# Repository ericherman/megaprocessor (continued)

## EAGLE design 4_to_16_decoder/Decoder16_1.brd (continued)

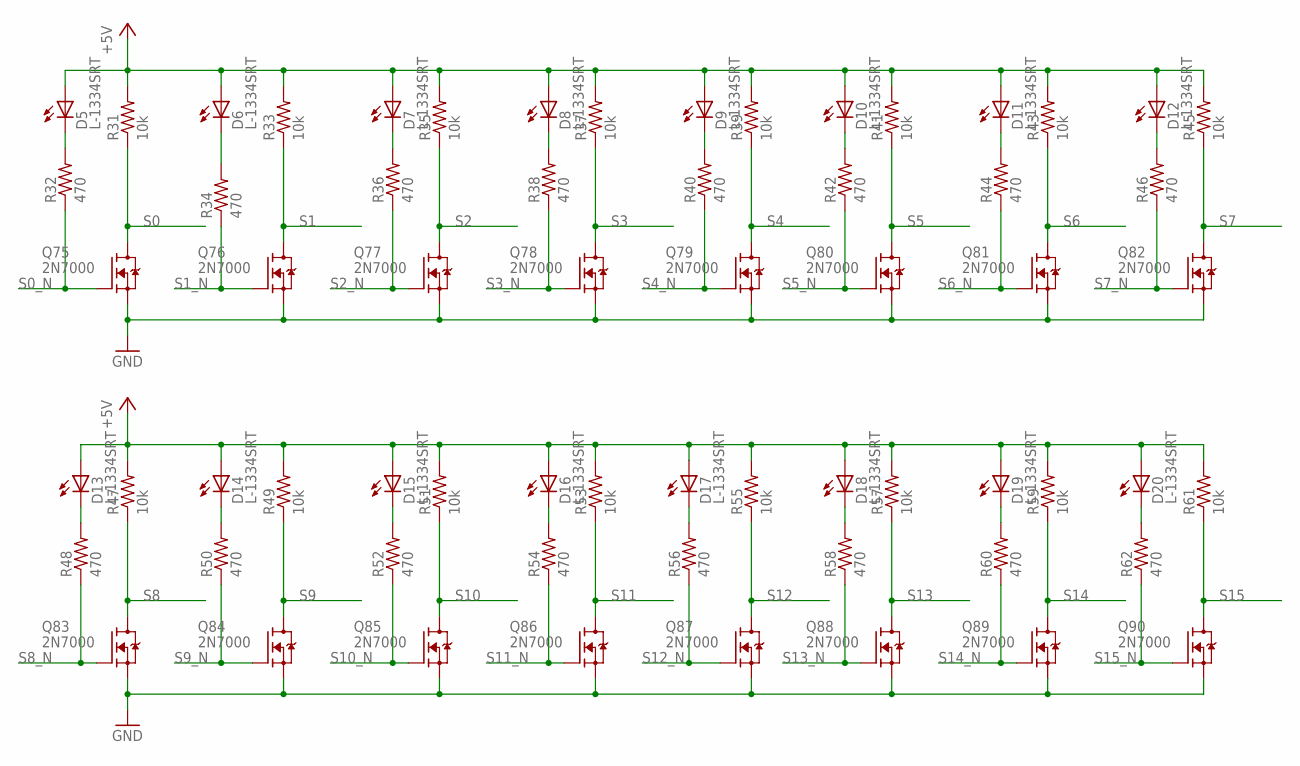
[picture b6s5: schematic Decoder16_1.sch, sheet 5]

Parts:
D5, D6, D7, D8, D9, D10, D11, D12, D13, D14, D15, D16, D17, D18, D19, D20: L-1334SRT; LED3MM
Q75, Q76, Q77, Q78, Q79, Q80, Q81, Q82, Q83, Q84, Q85, Q86, Q87, Q88, Q89, Q90: 2N7000; TO92-DGS
R31, R33, R35, R37, R39, R41, R43, R45, R47, R49, R51, R53, R55, R57, R59, R61: 10k; R_P2INCH
R32, R34, R36, R38, R40, R42, R44, R46, R48, R50, R52, R54, R56, R58, R60, R62: 470; R_P2INCH

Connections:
+5V: D5.A, D6.A, D7.A, D8.A, D9.A, D10.A, D11.A, D12.A, D13.A, D14.A, D15.A, D16.A, D17.A, D18.A, D19.A, D20.A, R31.2, R33.2, R35.2, R37.2, R39.2, R41.2, R43.2, R45.2, R47.2, R49.2, R51.2, R53.2, R55.2, R57.2, R59.2, R61.2; also elsewhere on the board
GND: Q75.S, Q76.S, Q77.S, Q78.S, Q79.S, Q80.S, Q81.S, Q82.S, Q83.S, Q84.S, Q85.S, Q86.S, Q87.S, Q88.S, Q89.S, Q90.S; also elsewhere on the board
unnamed: D5.K (C), R32.2
unnamed: D13.K (C), R48.2
unnamed: D6.K (C), R34.2
unnamed: D14.K (C), R50.2
unnamed: D7.K (C), R36.2
unnamed: D15.K (C), R52.2
unnamed: D8.K (C), R38.2
unnamed: D16.K (C), R54.2
unnamed: D9.K (C), R40.2
unnamed: D17.K (C), R56.2
unnamed: D10.K (C), R42.2
unnamed: D18.K (C), R58.2
unnamed: D11.K (C), R44.2
unnamed: D19.K (C), R60.2
unnamed: D12.K (C), R46.2
unnamed: D20.K (C), R62.2
S0: Q75.D, R31.1; also elsewhere on the board
S0_N: Q75.G, R32.1; also elsewhere on the board
S1: Q76.D, R33.1; also elsewhere on the board
S1_N: Q76.G, R34.1; also elsewhere on the board
S2: Q77.D, R35.1; also elsewhere on the board
S2_N: Q77.G, R36.1; also elsewhere on the board
S3: Q78.D, R37.1; also elsewhere on the board
S3_N: Q78.G, R38.1; also elsewhere on the board
S4: Q79.D, R39.1; also elsewhere on the board
S4_N: Q79.G, R40.1; also elsewhere on the board
S5: Q80.D, R41.1; also elsewhere on the board
S5_N: Q80.G, R42.1; also elsewhere on the board
S6: Q81.D, R43.1; also elsewhere on the board
S6_N: Q81.G, R44.1; also elsewhere on the board
S7: Q82.D, R45.1; also elsewhere on the board
S7_N: Q82.G, R46.1; also elsewhere on the board
S8: Q83.D, R47.1; also elsewhere on the board
S8_N: Q83.G, R48.1; also elsewhere on the board
S9: Q84.D, R49.1; also elsewhere on the board
S9_N: Q84.G, R50.1; also elsewhere on the board
S10: Q85.D, R51.1; also elsewhere on the board
S10_N: Q85.G, R52.1; also elsewhere on the board
S11: Q86.D, R53.1; also elsewhere on the board
S11_N: Q86.G, R54.1; also elsewhere on the board
S12: Q87.D, R55.1; also elsewhere on the board
S12_N: Q87.G, R56.1; also elsewhere on the board
S13: Q88.D, R57.1; also elsewhere on the board
S13_N: Q88.G, R58.1; also elsewhere on the board
S14: Q89.D, R59.1; also elsewhere on the board
S14_N: Q89.G, R60.1; also elsewhere on the board
S15: Q90.D, R61.1; also elsewhere on the board
S15_N: Q90.G, R62.1; also elsewhere on the board

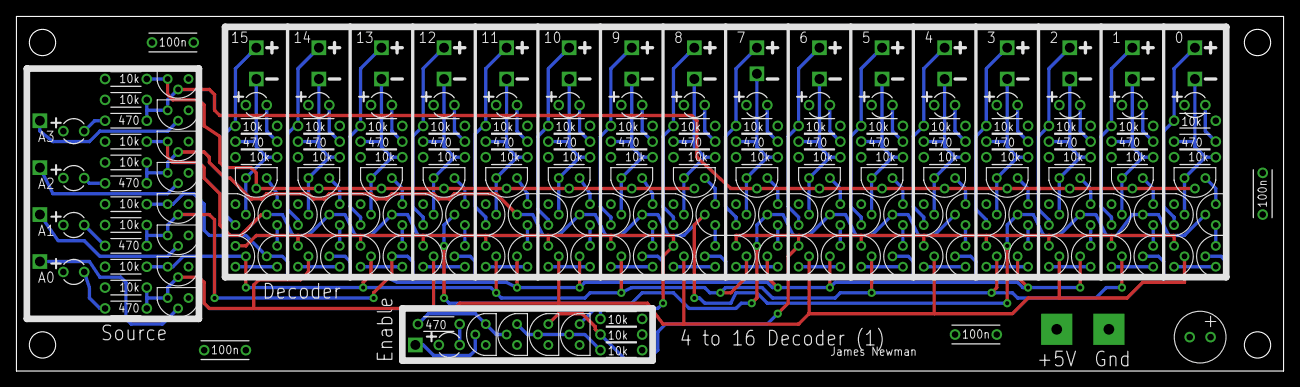
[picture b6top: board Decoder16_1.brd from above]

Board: 4 copper layers, 154.3 x 43.2 mm, 225 parts (0 on the bottom side), 120 nets.

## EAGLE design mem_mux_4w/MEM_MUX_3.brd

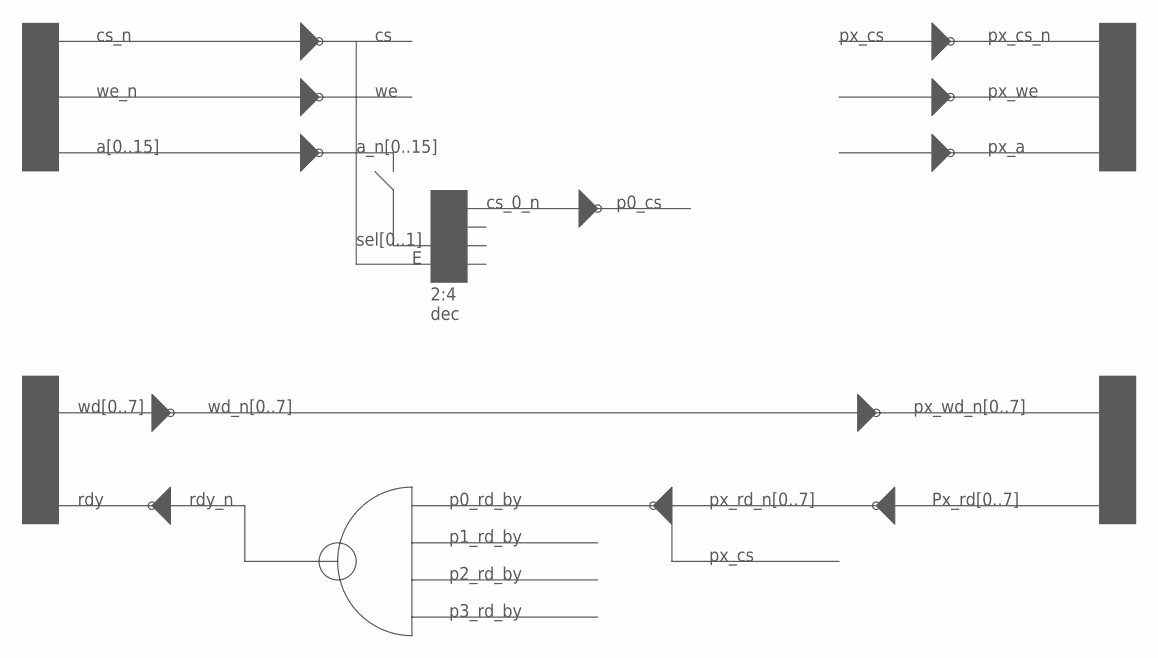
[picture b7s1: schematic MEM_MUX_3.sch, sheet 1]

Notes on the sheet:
cs_n
we_n
a[0..15]
a_n[0..15]
2:4 dec
cs_0_n
p0_cs
sel[0..1]
px_a
px_we
px_cs
px_cs_n
wd[0..7]
wd_n[0..7]
px_wd_n[0..7]
Px_rd[0..7]
px_rd_n[0..7]
p0_rd_by
p1_rd_by
p2_rd_by
p3_rd_by
rdy_n
rdy

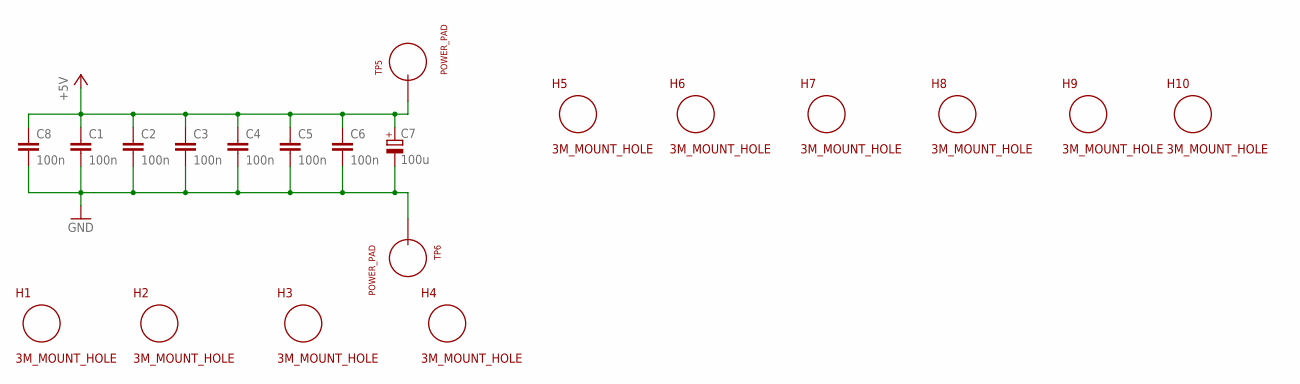
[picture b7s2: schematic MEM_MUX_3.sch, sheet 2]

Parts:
C1, C2, C3, C4, C5, C6, C8: 100n; CAP_P2INCH
C7: 100u; POLARISED_CAP_2P5_6P3MM
H1, H2, H3, H4, H5, H6, H7, H8, H9, H10: 3M_MOUNT_HOLE; 3M_HOLE
TP5, TP6: POWER_PAD

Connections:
+5V: C1.1, C2.1, C3.1, C4.1, C5.1, C6.1, C7.A, C8.1, TP5.1; also elsewhere on the board
GND: C1.2, C2.2, C3.2, C4.2, C5.2, C6.2, C7.K, C8.2, TP6.1; also elsewhere on the board

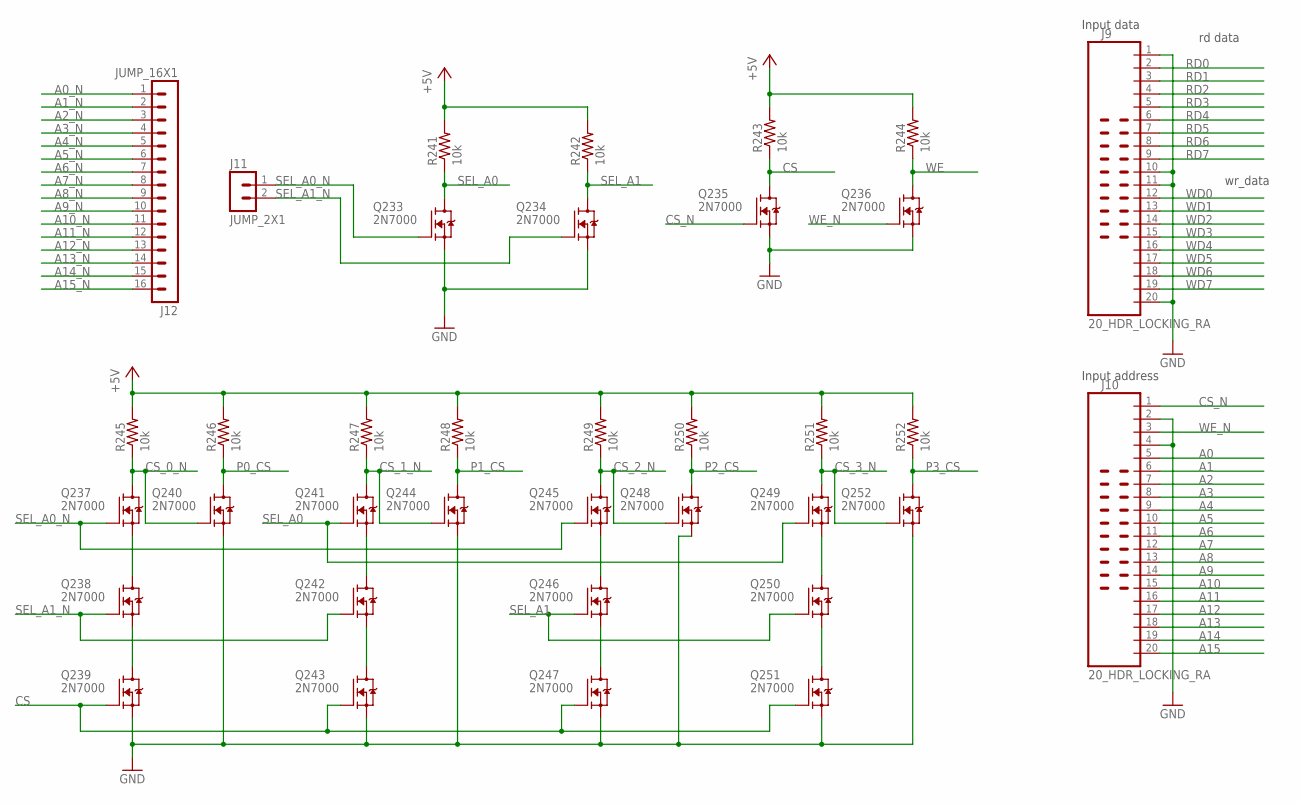
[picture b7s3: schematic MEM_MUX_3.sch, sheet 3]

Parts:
J9, J10: 20_HDR_LOCKING_RA
J11: JUMP_2X1
J12: JUMP_16X1
Q233, Q234, Q235, Q236, Q237, Q238, Q239, Q240, Q241, Q242, Q243, Q244, Q245, Q246, Q247, Q248, Q249, Q250, Q251, Q252: 2N7000; TO92-DGS
R241, R242, R243, R244, R245, R246, R247, R248, R249, R250, R251, R252: 10k; R_P2INCH

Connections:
+5V: R241.2, R242.2, R243.2, R244.2, R245.2, R246.2, R247.2, R248.2, R249.2, R250.2, R251.2, R252.2; also elsewhere on the board
A0: J10.5; also elsewhere on the board
A0_N: J12.1; also elsewhere on the board
A1: J10.6; also elsewhere on the board
A1_N: J12.2; also elsewhere on the board
A2: J10.7; also elsewhere on the board
A2_N: J12.3; also elsewhere on the board
A3: J10.8; also elsewhere on the board
A3_N: J12.4; also elsewhere on the board
A4: J10.9; also elsewhere on the board
A4_N: J12.5; also elsewhere on the board
A5: J10.10; also elsewhere on the board
A5_N: J12.6; also elsewhere on the board
A6: J10.11; also elsewhere on the board
A6_N: J12.7; also elsewhere on the board
A7: J10.12; also elsewhere on the board
A7_N: J12.8; also elsewhere on the board
A8: J10.13; also elsewhere on the board
A8_N: J12.9; also elsewhere on the board
A9: J10.14; also elsewhere on the board
A9_N: J12.10; also elsewhere on the board
A10: J10.15; also elsewhere on the board
A10_N: J12.11; also elsewhere on the board
A11: J10.16; also elsewhere on the board
A11_N: J12.12; also elsewhere on the board
A12: J10.17; also elsewhere on the board
A12_N: J12.13; also elsewhere on the board
A13: J10.18; also elsewhere on the board
A13_N: J12.14; also elsewhere on the board
A14: J10.19; also elsewhere on the board
A14_N: J12.15; also elsewhere on the board
A15: J10.20; also elsewhere on the board
A15_N: J12.16; also elsewhere on the board
CS: Q235.D, Q239.G, Q243.G, Q247.G, Q251.G, R243.1
CS_0_N: Q237.D, Q240.G, R245.1; also elsewhere on the board
CS_1_N: Q241.D, Q244.G, R247.1; also elsewhere on the board
CS_2_N: Q245.D, Q248.G, R249.1; also elsewhere on the board
CS_3_N: Q249.D, Q252.G, R251.1; also elsewhere on the board
CS_N: J10.1, Q235.G
GND: J9.1, J9.10, J9.11, J9.20, J10.2, J10.4, Q233.S, Q234.S, Q235.S, Q236.S, Q239.S, Q240.S, Q243.S, Q244.S, Q247.S, Q248.S, Q251.S, Q252.S; also elsewhere on the board
unnamed: Q241.S, Q242.D
unnamed: Q237.S, Q238.D
unnamed: Q238.S, Q239.D
unnamed: Q242.S, Q243.D
unnamed: Q245.S, Q246.D
unnamed: Q246.S, Q247.D
unnamed: Q249.S, Q250.D
unnamed: Q250.S, Q251.D
P0_CS: Q240.D, R246.1; also elsewhere on the board
P1_CS: Q244.D, R248.1; also elsewhere on the board
P2_CS: Q248.D, R250.1; also elsewhere on the board
P3_CS: Q252.D, R252.1; also elsewhere on the board
RD0: J9.2; also elsewhere on the board
RD1: J9.3; also elsewhere on the board
RD2: J9.4; also elsewhere on the board
RD3: J9.5; also elsewhere on the board
RD4: J9.6; also elsewhere on the board
RD5: J9.7; also elsewhere on the board
RD6: J9.8; also elsewhere on the board
RD7: J9.9; also elsewhere on the board
SEL_A0: Q233.D, Q241.G, Q249.G, R241.1
SEL_A0_N: J11.1, Q233.G, Q237.G, Q245.G
SEL_A1: Q234.D, Q246.G, Q250.G, R242.1
SEL_A1_N: J11.2, Q234.G, Q238.G, Q242.G
WD0: J9.12; also elsewhere on the board
WD1: J9.13; also elsewhere on the board
WD2: J9.14; also elsewhere on the board
WD3: J9.15; also elsewhere on the board
WD4: J9.16; also elsewhere on the board
WD5: J9.17; also elsewhere on the board
WD6: J9.18; also elsewhere on the board
WD7: J9.19; also elsewhere on the board
WE: Q236.D, R244.1; also elsewhere on the board
WE_N: J10.3, Q236.G

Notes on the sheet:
Input data
Input address
rd data
wr_data

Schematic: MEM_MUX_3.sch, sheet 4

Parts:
Q209, Q210, Q211, Q212, Q213, Q214, Q215, Q216, Q217, Q218, Q219, Q220, Q221, Q222, Q223, Q224, Q225, Q226, Q227, Q228, Q229, Q230, Q231, Q232: 2N7000; TO92-DGS
R217, R218, R219, R220, R221, R222, R223, R224, R225, R226, R227, R228, R229, R230, R231, R232, R233, R234, R235, R236, R237, R238, R239, R240: 10k; R_P2INCH

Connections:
+5V: R217.2, R218.2, R219.2, R220.2, R221.2, R222.2, R223.2, R224.2, R225.2, R226.2, R227.2, R228.2, R229.2, R230.2, R231.2, R232.2, R233.2, R234.2, R235.2, R236.2, R237.2, R238.2, R239.2, R240.2; also elsewhere on the board
A0: Q217.G; also elsewhere on the board
A0_N: Q217.D, R225.1; also elsewhere on the board
A1: Q218.G; also elsewhere on the board
A1_N: Q218.D, R226.1; also elsewhere on the board
A2: Q219.G; also elsewhere on the board
A2_N: Q219.D, R227.1; also elsewhere on the board
A3: Q220.G; also elsewhere on the board
A3_N: Q220.D, R228.1; also elsewhere on the board
A4: Q221.G; also elsewhere on the board
A4_N: Q221.D, R229.1; also elsewhere on the board
A5: Q222.G; also elsewhere on the board
A5_N: Q222.D, R230.1; also elsewhere on the board
A6: Q223.G; also elsewhere on the board
A6_N: Q223.D, R231.1; also elsewhere on the board
A7: Q224.G; also elsewhere on the board
A7_N: Q224.D, R232.1; also elsewhere on the board
A8: Q225.G; also elsewhere on the board
A8_N: Q225.D, R233.1; also elsewhere on the board
A9: Q226.G; also elsewhere on the board
A9_N: Q226.D, R234.1; also elsewhere on the board
A10: Q227.G; also elsewhere on the board
A10_N: Q227.D, R235.1; also elsewhere on the board
A11: Q228.G; also elsewhere on the board
A11_N: Q228.D, R236.1; also elsewhere on the board
A12: Q229.G; also elsewhere on the board
A12_N: Q229.D, R237.1; also elsewhere on the board
A13: Q230.G; also elsewhere on the board
A13_N: Q230.D, R238.1; also elsewhere on the board
A14: Q231.G; also elsewhere on the board
A14_N: Q231.D, R239.1; also elsewhere on the board
A15: Q232.G; also elsewhere on the board
A15_N: Q232.D, R240.1; also elsewhere on the board
GND: Q209.S, Q210.S, Q211.S, Q212.S, Q213.S, Q214.S, Q215.S, Q216.S, Q217.S, Q218.S, Q219.S, Q220.S, Q221.S, Q222.S, Q223.S, Q224.S, Q225.S, Q226.S, Q227.S, Q228.S, Q229.S, Q230.S, Q231.S, Q232.S; also elsewhere on the board
WD0: Q209.G; also elsewhere on the board
WD0_N: Q209.D, R217.1; also elsewhere on the board
WD1: Q210.G; also elsewhere on the board
WD1_N: Q210.D, R218.1; also elsewhere on the board
WD2: Q211.G; also elsewhere on the board
WD2_N: Q211.D, R219.1; also elsewhere on the board
WD3: Q212.G; also elsewhere on the board
WD3_N: Q212.D, R220.1; also elsewhere on the board
WD4: Q213.G; also elsewhere on the board
WD4_N: Q213.D, R221.1; also elsewhere on the board
WD5: Q214.G; also elsewhere on the board
WD5_N: Q214.D, R222.1; also elsewhere on the board
WD6: Q215.G; also elsewhere on the board
WD6_N: Q215.D, R223.1; also elsewhere on the board
WD7: Q216.G; also elsewhere on the board
WD7_N: Q216.D, R224.1; also elsewhere on the board

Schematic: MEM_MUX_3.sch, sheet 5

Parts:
D1, D2, D3, D4, D5, D6, D7, D8: L-1334SRT; LED3MM
Q1, Q2, Q3, Q4, Q5, Q6, Q7, Q8, Q9, Q10, Q11, Q12, Q13, Q14, Q15, Q16: 2N7000; TO92-DGS
R1, R3, R5, R7, R9, R11, R13, R15, R17, R18, R19, R20, R21, R22, R23, R24: 10k; R_P2INCH
R2, R4, R6, R8, R10, R12, R14, R16: 470; R_P2INCH

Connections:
+5V: D1.A, D2.A, D3.A, D4.A, D5.A, D6.A, D7.A, D8.A, R1.2, R3.2, R5.2, R7.2, R9.2, R11.2, R13.2, R15.2, R17.2, R18.2, R19.2, R20.2, R21.2, R22.2, R23.2, R24.2; also elsewhere on the board
CS_0_N: Q2.S, Q4.S, Q6.S, Q8.S, Q10.S, Q12.S, Q14.S, Q16.S; also elsewhere on the board
GND: Q1.S, Q3.S, Q5.S, Q7.S, Q9.S, Q11.S, Q13.S, Q15.S; also elsewhere on the board
unnamed: Q3.D, Q4.G, R3.1, R4.1
unnamed: Q1.D, Q2.G, R1.1, R2.1
unnamed: D1.K (C), R2.2
unnamed: D2.K (C), R4.2
unnamed: Q5.D, Q6.G, R5.1, R6.1
unnamed: D3.K (C), R6.2
unnamed: Q7.D, Q8.G, R7.1, R8.1
unnamed: D4.K (C), R8.2
unnamed: Q9.D, Q10.G, R9.1, R10.1
unnamed: D5.K (C), R10.2
unnamed: Q11.D, Q12.G, R11.1, R12.1
unnamed: D6.K (C), R12.2
unnamed: Q13.D, Q14.G, R13.1, R14.1
unnamed: D7.K (C), R14.2
unnamed: Q15.D, Q16.G, R15.1, R16.1
unnamed: D8.K (C), R16.2
P0_RD0: Q1.G; also elsewhere on the board
P0_RD0_B: Q2.D, R17.1; also elsewhere on the board
P0_RD1: Q3.G; also elsewhere on the board
P0_RD1_B: Q4.D, R18.1; also elsewhere on the board
P0_RD2: Q5.G; also elsewhere on the board
P0_RD2_B: Q6.D, R19.1; also elsewhere on the board
P0_RD3: Q7.G; also elsewhere on the board
P0_RD3_B: Q8.D, R20.1; also elsewhere on the board
P0_RD4: Q9.G; also elsewhere on the board
P0_RD4_B: Q10.D, R21.1; also elsewhere on the board
P0_RD5: Q11.G; also elsewhere on the board
P0_RD5_B: Q12.D, R22.1; also elsewhere on the board
P0_RD6: Q13.G; also elsewhere on the board
P0_RD6_B: Q14.D, R23.1; also elsewhere on the board
P0_RD7: Q15.G; also elsewhere on the board
P0_RD7_B: Q16.D, R24.1; also elsewhere on the board

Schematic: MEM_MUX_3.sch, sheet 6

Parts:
J1, J2: 20_HDR_LOCKING_RA
Q23, Q24: 2N7000; TO92-DGS
R31, R32: 10k; R_P2INCH

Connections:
+5V: R31.2, R32.2; also elsewhere on the board
GND: J1.1, J1.10, J1.11, J1.20, J2.2, J2.4, Q23.S, Q24.S; also elsewhere on the board
P0_A0: J2.5; also elsewhere on the board
P0_A1: J2.6; also elsewhere on the board
P0_A2: J2.7; also elsewhere on the board
P0_A3: J2.8; also elsewhere on the board
P0_A4: J2.9; also elsewhere on the board
P0_A5: J2.10; also elsewhere on the board
P0_A6: J2.11; also elsewhere on the board
P0_A7: J2.12; also elsewhere on the board
P0_A8: J2.13; also elsewhere on the board
P0_A9: J2.14; also elsewhere on the board
P0_A10: J2.15; also elsewhere on the board
P0_A11: J2.16; also elsewhere on the board
P0_A12: J2.17; also elsewhere on the board
P0_A13: J2.18; also elsewhere on the board
P0_A14: J2.19; also elsewhere on the board
P0_A15: J2.20; also elsewhere on the board
P0_CS: Q23.G; also elsewhere on the board
P0_CS_N: J2.1, Q23.D, R31.1
P0_RD0: J1.2; also elsewhere on the board
P0_RD1: J1.3; also elsewhere on the board
P0_RD2: J1.4; also elsewhere on the board
P0_RD3: J1.5; also elsewhere on the board
P0_RD4: J1.6; also elsewhere on the board
P0_RD5: J1.7; also elsewhere on the board
P0_RD6: J1.8; also elsewhere on the board
P0_RD7: J1.9; also elsewhere on the board
P0_WD0: J1.12; also elsewhere on the board
P0_WD1: J1.13; also elsewhere on the board
P0_WD2: J1.14; also elsewhere on the board
P0_WD3: J1.15; also elsewhere on the board
P0_WD4: J1.16; also elsewhere on the board
P0_WD5: J1.17; also elsewhere on the board
P0_WD6: J1.18; also elsewhere on the board
P0_WD7: J1.19; also elsewhere on the board
P0_WE_N: J2.3, Q24.D, R32.1
WE: Q24.G; also elsewhere on the board

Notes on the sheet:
Port 0 data
Port 0 address
rd data
wr_data

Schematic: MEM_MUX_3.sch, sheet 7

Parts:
Q17, Q18, Q19, Q20, Q21, Q22, Q25, Q26, Q27, Q28, Q29, Q30, Q31, Q32, Q33, Q34, Q35, Q36, Q37, Q38, Q39, Q40, Q41, Q42: 2N7000; TO92-DGS
R25, R26, R27, R28, R29, R30, R33, R34, R35, R36, R37, R38, R39, R40, R41, R42, R43, R44, R45, R46, R47, R48, R49, R50: 10k; R_P2INCH

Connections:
+5V: R25.2, R26.2, R27.2, R28.2, R29.2, R30.2, R33.2, R34.2, R35.2, R36.2, R37.2, R38.2, R39.2, R40.2, R41.2, R42.2, R43.2, R44.2, R45.2, R46.2, R47.2, R48.2, R49.2, R50.2; also elsewhere on the board
A0_N: Q17.G; also elsewhere on the board
A1_N: Q18.G; also elsewhere on the board
A2_N: Q19.G; also elsewhere on the board
A3_N: Q20.G; also elsewhere on the board
A4_N: Q21.G; also elsewhere on the board
A5_N: Q22.G; also elsewhere on the board
A6_N: Q33.G; also elsewhere on the board
A7_N: Q34.G; also elsewhere on the board
A8_N: Q35.G; also elsewhere on the board
A9_N: Q36.G; also elsewhere on the board
A10_N: Q37.G; also elsewhere on the board
A11_N: Q38.G; also elsewhere on the board
A12_N: Q39.G; also elsewhere on the board
A13_N: Q40.G; also elsewhere on the board
A14_N: Q41.G; also elsewhere on the board
A15_N: Q42.G; also elsewhere on the board
GND: Q17.S, Q18.S, Q19.S, Q20.S, Q21.S, Q22.S, Q25.S, Q26.S, Q27.S, Q28.S, Q29.S, Q30.S, Q31.S, Q32.S, Q33.S, Q34.S, Q35.S, Q36.S, Q37.S, Q38.S, Q39.S, Q40.S, Q41.S, Q42.S; also elsewhere on the board
P0_A0: Q17.D, R25.1; also elsewhere on the board
P0_A1: Q18.D, R26.1; also elsewhere on the board
P0_A2: Q19.D, R27.1; also elsewhere on the board
P0_A3: Q20.D, R28.1; also elsewhere on the board
P0_A4: Q21.D, R29.1; also elsewhere on the board
P0_A5: Q22.D, R30.1; also elsewhere on the board
P0_A6: Q33.D, R41.1; also elsewhere on the board
P0_A7: Q34.D, R42.1; also elsewhere on the board
P0_A8: Q35.D, R43.1; also elsewhere on the board
P0_A9: Q36.D, R44.1; also elsewhere on the board
P0_A10: Q37.D, R45.1; also elsewhere on the board
P0_A11: Q38.D, R46.1; also elsewhere on the board
P0_A12: Q39.D, R47.1; also elsewhere on the board
P0_A13: Q40.D, R48.1; also elsewhere on the board
P0_A14: Q41.D, R49.1; also elsewhere on the board
P0_A15: Q42.D, R50.1; also elsewhere on the board
P0_WD0: Q25.D, R33.1; also elsewhere on the board
P0_WD1: Q26.D, R34.1; also elsewhere on the board
P0_WD2: Q27.D, R35.1; also elsewhere on the board
P0_WD3: Q28.D, R36.1; also elsewhere on the board
P0_WD4: Q29.D, R37.1; also elsewhere on the board
P0_WD5: Q30.D, R38.1; also elsewhere on the board
P0_WD6: Q31.D, R39.1; also elsewhere on the board
P0_WD7: Q32.D, R40.1; also elsewhere on the board
WD0_N: Q25.G; also elsewhere on the board
WD1_N: Q26.G; also elsewhere on the board
WD2_N: Q27.G; also elsewhere on the board
WD3_N: Q28.G; also elsewhere on the board
WD4_N: Q29.G; also elsewhere on the board
WD5_N: Q30.G; also elsewhere on the board
WD6_N: Q31.G; also elsewhere on the board
WD7_N: Q32.G; also elsewhere on the board

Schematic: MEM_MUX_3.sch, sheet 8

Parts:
D9, D10, D11, D12, D13, D14, D15, D16: L-1334SRT; LED3MM
Q43, Q44, Q45, Q46, Q47, Q48, Q49, Q50, Q51, Q52, Q53, Q54, Q55, Q56, Q57, Q58: 2N7000; TO92-DGS
R51, R53, R55, R57, R59, R61, R63, R65, R67, R68, R69, R70, R71, R72, R73, R74: 10k; R_P2INCH
R52, R54, R56, R58, R60, R62, R64, R66: 470; R_P2INCH

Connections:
+5V: D9.A, D10.A, D11.A, D12.A, D13.A, D14.A, D15.A, D16.A, R51.2, R53.2, R55.2, R57.2, R59.2, R61.2, R63.2, R65.2, R67.2, R68.2, R69.2, R70.2, R71.2, R72.2, R73.2, R74.2; also elsewhere on the board
CS_1_N: Q44.S, Q46.S, Q48.S, Q50.S, Q52.S, Q54.S, Q56.S, Q58.S; also elsewhere on the board
GND: Q43.S, Q45.S, Q47.S, Q49.S, Q51.S, Q53.S, Q55.S, Q57.S; also elsewhere on the board
unnamed: Q43.D, Q44.G, R51.1, R52.1
unnamed: D9.K (C), R52.2
unnamed: Q45.D, Q46.G, R53.1, R54.1
unnamed: D10.K (C), R54.2
unnamed: Q47.D, Q48.G, R55.1, R56.1
unnamed: D11.K (C), R56.2
unnamed: Q49.D, Q50.G, R57.1, R58.1
unnamed: D12.K (C), R58.2
unnamed: Q51.D, Q52.G, R59.1, R60.1
unnamed: D13.K (C), R60.2
unnamed: Q53.D, Q54.G, R61.1, R62.1
unnamed: D14.K (C), R62.2
unnamed: Q55.D, Q56.G, R63.1, R64.1
unnamed: D15.K (C), R64.2
unnamed: Q57.D, Q58.G, R65.1, R66.1
unnamed: D16.K (C), R66.2
P1_RD0: Q43.G; also elsewhere on the board
P1_RD0_B: Q44.D, R67.1; also elsewhere on the board
P1_RD1: Q45.G; also elsewhere on the board
P1_RD1_B: Q46.D, R68.1; also elsewhere on the board
P1_RD2: Q47.G; also elsewhere on the board
P1_RD2_B: Q48.D, R69.1; also elsewhere on the board
P1_RD3: Q49.G; also elsewhere on the board
P1_RD3_B: Q50.D, R70.1; also elsewhere on the board
P1_RD4: Q51.G; also elsewhere on the board
P1_RD4_B: Q52.D, R71.1; also elsewhere on the board
P1_RD5: Q53.G; also elsewhere on the board
P1_RD5_B: Q54.D, R72.1; also elsewhere on the board
P1_RD6: Q55.G; also elsewhere on the board
P1_RD6_B: Q56.D, R73.1; also elsewhere on the board
P1_RD7: Q57.G; also elsewhere on the board
P1_RD7_B: Q58.D, R74.1; also elsewhere on the board

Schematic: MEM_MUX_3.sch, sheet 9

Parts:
J3, J4: 20_HDR_LOCKING_RA
Q59, Q60: 2N7000; TO92-DGS
R75, R76: 10k; R_P2INCH

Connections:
+5V: R75.2, R76.2; also elsewhere on the board
GND: J3.1, J3.10, J3.11, J3.20, J4.2, J4.4, Q59.S, Q60.S; also elsewhere on the board
P1_A0: J4.5; also elsewhere on the board
P1_A1: J4.6; also elsewhere on the board
P1_A2: J4.7; also elsewhere on the board
P1_A3: J4.8; also elsewhere on the board
P1_A4: J4.9; also elsewhere on the board
P1_A5: J4.10; also elsewhere on the board
P1_A6: J4.11; also elsewhere on the board
P1_A7: J4.12; also elsewhere on the board
P1_A8: J4.13; also elsewhere on the board
P1_A9: J4.14; also elsewhere on the board
P1_A10: J4.15; also elsewhere on the board
P1_A11: J4.16; also elsewhere on the board
P1_A12: J4.17; also elsewhere on the board
P1_A13: J4.18; also elsewhere on the board
P1_A14: J4.19; also elsewhere on the board
P1_A15: J4.20; also elsewhere on the board
P1_CS: Q59.G; also elsewhere on the board
P1_CS_N: J4.1, Q59.D, R75.1
P1_RD0: J3.2; also elsewhere on the board
P1_RD1: J3.3; also elsewhere on the board
P1_RD2: J3.4; also elsewhere on the board
P1_RD3: J3.5; also elsewhere on the board
P1_RD4: J3.6; also elsewhere on the board
P1_RD5: J3.7; also elsewhere on the board
P1_RD6: J3.8; also elsewhere on the board
P1_RD7: J3.9; also elsewhere on the board
P1_WD0: J3.12; also elsewhere on the board
P1_WD1: J3.13; also elsewhere on the board
P1_WD2: J3.14; also elsewhere on the board
P1_WD3: J3.15; also elsewhere on the board
P1_WD4: J3.16; also elsewhere on the board
P1_WD5: J3.17; also elsewhere on the board
P1_WD6: J3.18; also elsewhere on the board
P1_WD7: J3.19; also elsewhere on the board
P1_WE_N: J4.3, Q60.D, R76.1
WE: Q60.G; also elsewhere on the board

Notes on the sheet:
Port 1 data
Port 1 address
rd data
wr_data

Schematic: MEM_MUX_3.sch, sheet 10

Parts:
Q61, Q62, Q63, Q64, Q65, Q66, Q67, Q68, Q69, Q70, Q71, Q72, Q73, Q74, Q75, Q76, Q77, Q78, Q79, Q80, Q81, Q82, Q83, Q84: 2N7000; TO92-DGS
R77, R78, R79, R80, R81, R82, R83, R84, R85, R86, R87, R88, R89, R90, R91, R92, R93, R94, R95, R96, R97, R98, R99, R100: 10k; R_P2INCH

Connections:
+5V: R77.2, R78.2, R79.2, R80.2, R81.2, R82.2, R83.2, R84.2, R85.2, R86.2, R87.2, R88.2, R89.2, R90.2, R91.2, R92.2, R93.2, R94.2, R95.2, R96.2, R97.2, R98.2, R99.2, R100.2; also elsewhere on the board
A0_N: Q69.G; also elsewhere on the board
A1_N: Q70.G; also elsewhere on the board
A2_N: Q71.G; also elsewhere on the board
A3_N: Q72.G; also elsewhere on the board
A4_N: Q73.G; also elsewhere on the board
A5_N: Q74.G; also elsewhere on the board
A6_N: Q75.G; also elsewhere on the board
A7_N: Q76.G; also elsewhere on the board
A8_N: Q77.G; also elsewhere on the board
A9_N: Q78.G; also elsewhere on the board
A10_N: Q79.G; also elsewhere on the board
A11_N: Q80.G; also elsewhere on the board
A12_N: Q81.G; also elsewhere on the board
A13_N: Q82.G; also elsewhere on the board
A14_N: Q83.G; also elsewhere on the board
A15_N: Q84.G; also elsewhere on the board
GND: Q61.S, Q62.S, Q63.S, Q64.S, Q65.S, Q66.S, Q67.S, Q68.S, Q69.S, Q70.S, Q71.S, Q72.S, Q73.S, Q74.S, Q75.S, Q76.S, Q77.S, Q78.S, Q79.S, Q80.S, Q81.S, Q82.S, Q83.S, Q84.S; also elsewhere on the board
P1_A0: Q69.D, R85.1; also elsewhere on the board
P1_A1: Q70.D, R86.1; also elsewhere on the board
P1_A2: Q71.D, R87.1; also elsewhere on the board
P1_A3: Q72.D, R88.1; also elsewhere on the board
P1_A4: Q73.D, R89.1; also elsewhere on the board
P1_A5: Q74.D, R90.1; also elsewhere on the board
P1_A6: Q75.D, R91.1; also elsewhere on the board
P1_A7: Q76.D, R92.1; also elsewhere on the board
P1_A8: Q77.D, R93.1; also elsewhere on the board
P1_A9: Q78.D, R94.1; also elsewhere on the board
P1_A10: Q79.D, R95.1; also elsewhere on the board
P1_A11: Q80.D, R96.1; also elsewhere on the board
P1_A12: Q81.D, R97.1; also elsewhere on the board
P1_A13: Q82.D, R98.1; also elsewhere on the board
P1_A14: Q83.D, R99.1; also elsewhere on the board
P1_A15: Q84.D, R100.1; also elsewhere on the board
P1_WD0: Q61.D, R77.1; also elsewhere on the board
P1_WD1: Q62.D, R78.1; also elsewhere on the board
P1_WD2: Q63.D, R79.1; also elsewhere on the board
P1_WD3: Q64.D, R80.1; also elsewhere on the board
P1_WD4: Q65.D, R81.1; also elsewhere on the board
P1_WD5: Q66.D, R82.1; also elsewhere on the board
P1_WD6: Q67.D, R83.1; also elsewhere on the board
P1_WD7: Q68.D, R84.1; also elsewhere on the board
WD0_N: Q61.G; also elsewhere on the board
WD1_N: Q62.G; also elsewhere on the board
WD2_N: Q63.G; also elsewhere on the board
WD3_N: Q64.G; also elsewhere on the board
WD4_N: Q65.G; also elsewhere on the board
WD5_N: Q66.G; also elsewhere on the board
WD6_N: Q67.G; also elsewhere on the board
WD7_N: Q68.G; also elsewhere on the board

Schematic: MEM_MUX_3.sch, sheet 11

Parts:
D17, D18, D19, D20, D21, D22, D23, D24: L-1334SRT; LED3MM
Q85, Q86, Q87, Q88, Q89, Q90, Q91, Q92, Q93, Q94, Q95, Q96, Q97, Q98, Q99, Q100: 2N7000; TO92-DGS
R101, R103, R105, R107, R109, R111, R113, R115, R117, R118, R119, R120, R121, R122, R123, R124: 10k; R_P2INCH
R102, R104, R106, R108, R110, R112, R114, R116: 470; R_P2INCH

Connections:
+5V: D17.A, D18.A, D19.A, D20.A, D21.A, D22.A, D23.A, D24.A, R101.2, R103.2, R105.2, R107.2, R109.2, R111.2, R113.2, R115.2, R117.2, R118.2, R119.2, R120.2, R121.2, R122.2, R123.2, R124.2; also elsewhere on the board
CS_2_N: Q86.S, Q88.S, Q90.S, Q92.S, Q94.S, Q96.S, Q98.S, Q100.S; also elsewhere on the board
GND: Q85.S, Q87.S, Q89.S, Q91.S, Q93.S, Q95.S, Q97.S, Q99.S; also elsewhere on the board
unnamed: Q85.D, Q86.G, R101.1, R102.1
unnamed: D17.K (C), R102.2
unnamed: Q87.D, Q88.G, R103.1, R104.1
unnamed: D18.K (C), R104.2
unnamed: Q89.D, Q90.G, R105.1, R106.1
unnamed: D19.K (C), R106.2
unnamed: Q91.D, Q92.G, R107.1, R108.1
unnamed: D20.K (C), R108.2
unnamed: Q93.D, Q94.G, R109.1, R110.1
unnamed: D21.K (C), R110.2
unnamed: Q95.D, Q96.G, R111.1, R112.1
unnamed: D22.K (C), R112.2
unnamed: Q97.D, Q98.G, R113.1, R114.1
unnamed: D23.K (C), R114.2
unnamed: Q99.D, Q100.G, R115.1, R116.1
unnamed: D24.K (C), R116.2
P2_RD0: Q85.G; also elsewhere on the board
P2_RD0_B: Q86.D, R117.1; also elsewhere on the board
P2_RD1: Q87.G; also elsewhere on the board
P2_RD1_B: Q88.D, R118.1; also elsewhere on the board
P2_RD2: Q89.G; also elsewhere on the board
P2_RD2_B: Q90.D, R119.1; also elsewhere on the board
P2_RD3: Q91.G; also elsewhere on the board
P2_RD3_B: Q92.D, R120.1; also elsewhere on the board
P2_RD4: Q93.G; also elsewhere on the board
P2_RD4_B: Q94.D, R121.1; also elsewhere on the board
P2_RD5: Q95.G; also elsewhere on the board
P2_RD5_B: Q96.D, R122.1; also elsewhere on the board
P2_RD6: Q97.G; also elsewhere on the board
P2_RD6_B: Q98.D, R123.1; also elsewhere on the board
P2_RD7: Q99.G; also elsewhere on the board
P2_RD7_B: Q100.D, R124.1; also elsewhere on the board

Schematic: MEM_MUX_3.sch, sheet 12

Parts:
J5, J6: 20_HDR_LOCKING_RA
Q101, Q102: 2N7000; TO92-DGS
R125, R126: 10k; R_P2INCH

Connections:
+5V: R125.2, R126.2; also elsewhere on the board
GND: J5.1, J5.10, J5.11, J5.20, J6.2, J6.4, Q101.S, Q102.S; also elsewhere on the board
P2_A0: J6.5; also elsewhere on the board
P2_A1: J6.6; also elsewhere on the board
P2_A2: J6.7; also elsewhere on the board
P2_A3: J6.8; also elsewhere on the board
P2_A4: J6.9; also elsewhere on the board
P2_A5: J6.10; also elsewhere on the board
P2_A6: J6.11; also elsewhere on the board
P2_A7: J6.12; also elsewhere on the board
P2_A8: J6.13; also elsewhere on the board
P2_A9: J6.14; also elsewhere on the board
P2_A10: J6.15; also elsewhere on the board
P2_A11: J6.16; also elsewhere on the board
P2_A12: J6.17; also elsewhere on the board
P2_A13: J6.18; also elsewhere on the board
P2_A14: J6.19; also elsewhere on the board
P2_A15: J6.20; also elsewhere on the board
P2_CS: Q101.G; also elsewhere on the board
P2_CS_N: J6.1, Q101.D, R125.1
P2_RD0: J5.2; also elsewhere on the board
P2_RD1: J5.3; also elsewhere on the board
P2_RD2: J5.4; also elsewhere on the board
P2_RD3: J5.5; also elsewhere on the board
P2_RD4: J5.6; also elsewhere on the board
P2_RD5: J5.7; also elsewhere on the board
P2_RD6: J5.8; also elsewhere on the board
P2_RD7: J5.9; also elsewhere on the board
P2_WD0: J5.12; also elsewhere on the board
P2_WD1: J5.13; also elsewhere on the board
P2_WD2: J5.14; also elsewhere on the board
P2_WD3: J5.15; also elsewhere on the board
P2_WD4: J5.16; also elsewhere on the board
P2_WD5: J5.17; also elsewhere on the board
P2_WD6: J5.18; also elsewhere on the board
P2_WD7: J5.19; also elsewhere on the board
P2_WE_N: J6.3, Q102.D, R126.1
WE: Q102.G; also elsewhere on the board

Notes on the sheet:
Port 1 data
Port 1 address
rd data
wr_data

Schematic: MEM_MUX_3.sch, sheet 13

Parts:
Q103, Q104, Q105, Q106, Q107, Q108, Q109, Q110, Q111, Q112, Q113, Q114, Q115, Q116, Q117, Q118, Q119, Q120, Q121, Q122, Q123, Q124, Q125, Q126: 2N7000; TO92-DGS
R127, R128, R129, R130, R131, R132, R133, R134, R135, R136, R137, R138, R139, R140, R141, R142, R143, R144, R145, R146, R147, R148, R149, R150: 10k; R_P2INCH

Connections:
+5V: R127.2, R128.2, R129.2, R130.2, R131.2, R132.2, R133.2, R134.2, R135.2, R136.2, R137.2, R138.2, R139.2, R140.2, R141.2, R142.2, R143.2, R144.2, R145.2, R146.2, R147.2, R148.2, R149.2, R150.2; also elsewhere on the board
A0_N: Q111.G; also elsewhere on the board
A1_N: Q112.G; also elsewhere on the board
A2_N: Q113.G; also elsewhere on the board
A3_N: Q114.G; also elsewhere on the board
A4_N: Q115.G; also elsewhere on the board
A5_N: Q116.G; also elsewhere on the board
A6_N: Q117.G; also elsewhere on the board
A7_N: Q118.G; also elsewhere on the board
A8_N: Q119.G; also elsewhere on the board
A9_N: Q120.G; also elsewhere on the board
A10_N: Q121.G; also elsewhere on the board
A11_N: Q122.G; also elsewhere on the board
A12_N: Q123.G; also elsewhere on the board
A13_N: Q124.G; also elsewhere on the board
A14_N: Q125.G; also elsewhere on the board
A15_N: Q126.G; also elsewhere on the board
GND: Q103.S, Q104.S, Q105.S, Q106.S, Q107.S, Q108.S, Q109.S, Q110.S, Q111.S, Q112.S, Q113.S, Q114.S, Q115.S, Q116.S, Q117.S, Q118.S, Q119.S, Q120.S, Q121.S, Q122.S, Q123.S, Q124.S, Q125.S, Q126.S; also elsewhere on the board
P2_A0: Q111.D, R135.1; also elsewhere on the board
P2_A1: Q112.D, R136.1; also elsewhere on the board
P2_A2: Q113.D, R137.1; also elsewhere on the board
P2_A3: Q114.D, R138.1; also elsewhere on the board
P2_A4: Q115.D, R139.1; also elsewhere on the board
P2_A5: Q116.D, R140.1; also elsewhere on the board
P2_A6: Q117.D, R141.1; also elsewhere on the board
P2_A7: Q118.D, R142.1; also elsewhere on the board
P2_A8: Q119.D, R143.1; also elsewhere on the board
P2_A9: Q120.D, R144.1; also elsewhere on the board
P2_A10: Q121.D, R145.1; also elsewhere on the board
P2_A11: Q122.D, R146.1; also elsewhere on the board
P2_A12: Q123.D, R147.1; also elsewhere on the board
P2_A13: Q124.D, R148.1; also elsewhere on the board
P2_A14: Q125.D, R149.1; also elsewhere on the board
P2_A15: Q126.D, R150.1; also elsewhere on the board
P2_WD0: Q103.D, R127.1; also elsewhere on the board
P2_WD1: Q104.D, R128.1; also elsewhere on the board
P2_WD2: Q105.D, R129.1; also elsewhere on the board
P2_WD3: Q106.D, R130.1; also elsewhere on the board
P2_WD4: Q107.D, R131.1; also elsewhere on the board
P2_WD5: Q108.D, R132.1; also elsewhere on the board
P2_WD6: Q109.D, R133.1; also elsewhere on the board
P2_WD7: Q110.D, R134.1; also elsewhere on the board
WD0_N: Q103.G; also elsewhere on the board
WD1_N: Q104.G; also elsewhere on the board
WD2_N: Q105.G; also elsewhere on the board
WD3_N: Q106.G; also elsewhere on the board
WD4_N: Q107.G; also elsewhere on the board
WD5_N: Q108.G; also elsewhere on the board
WD6_N: Q109.G; also elsewhere on the board
WD7_N: Q110.G; also elsewhere on the board
